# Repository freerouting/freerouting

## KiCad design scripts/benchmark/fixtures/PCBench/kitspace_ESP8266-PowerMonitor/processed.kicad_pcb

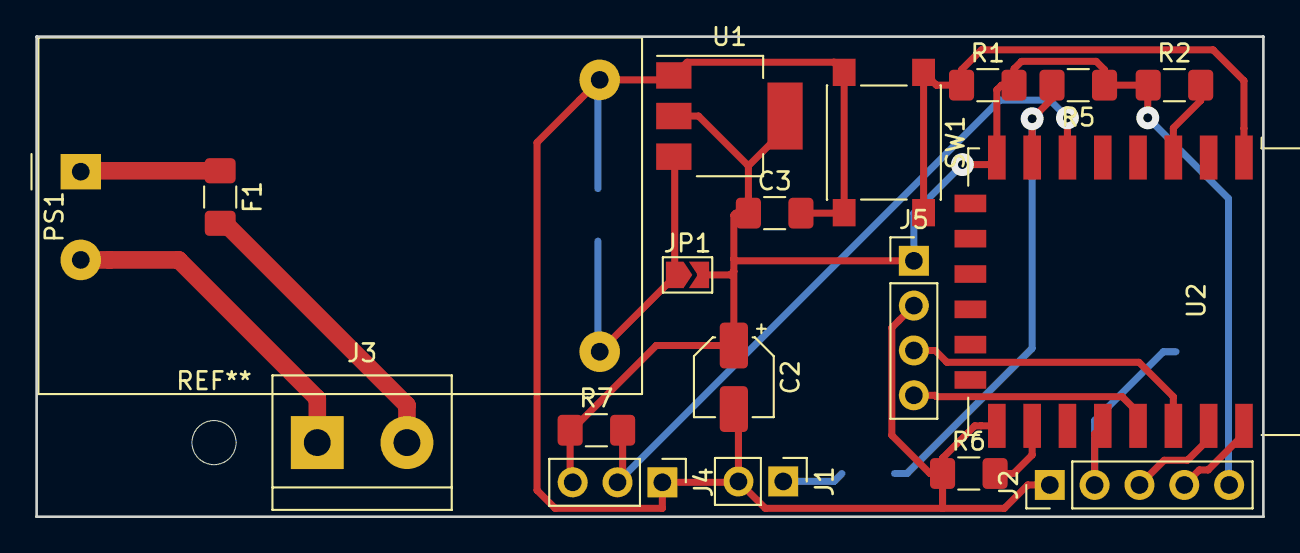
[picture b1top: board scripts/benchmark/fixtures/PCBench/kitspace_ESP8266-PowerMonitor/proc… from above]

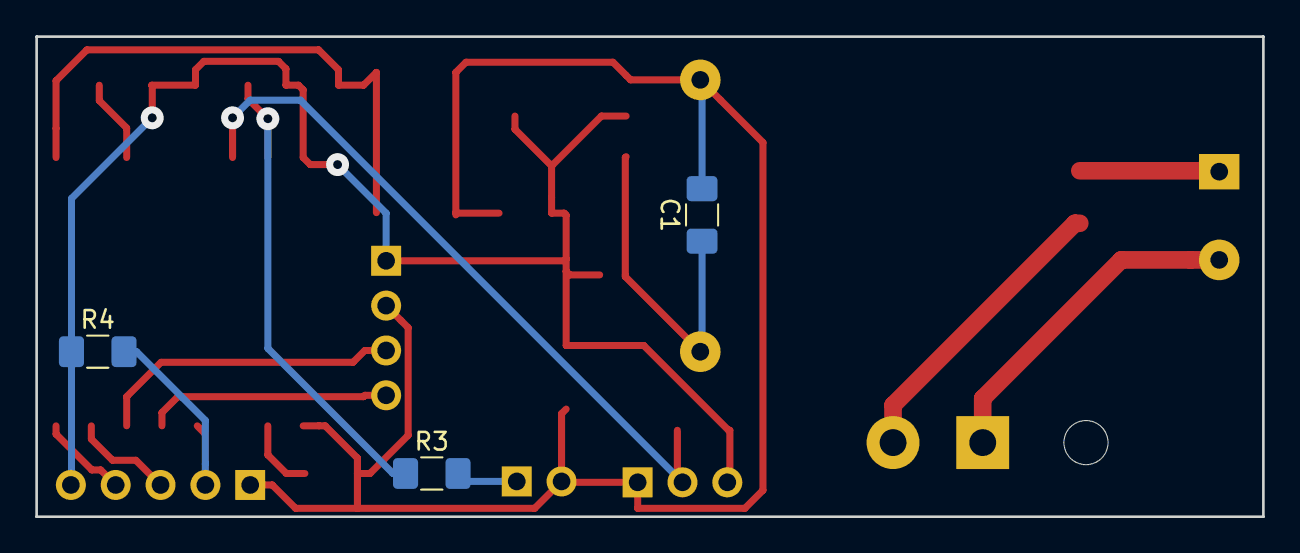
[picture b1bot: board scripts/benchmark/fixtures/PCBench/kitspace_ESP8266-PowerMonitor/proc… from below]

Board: 2 copper layers, 69.5 x 27.2 mm, 21 parts (3 on the bottom side), 17 nets.

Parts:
C1: 0.1uF; C_1206_3216Metric_Pad1.42x1.75mm_HandSolder
C2: 10uF; CP_Elec_4x5.3
C3: 100nF; C_1206_3216Metric_Pad1.42x1.75mm_HandSolder
F1: 100mA; Fuse_1206_3216Metric_Pad1.42x1.75mm_HandSolder
J1: CONN_PULSE; PinHeader_1x02_P2.54mm_Vertical
J2: CONN_PROG; PinHeader_1x05_P2.54mm_Vertical
J3: CONN_AC; TerminalBlock_bornier-2_P5.08mm
J4: CONN_TEMP; PinHeader_1x03_P2.54mm_Vertical
J5: CONN_I2C; PinHeader_1x04_P2.54mm_Vertical
JP1: 3.3V BYPASS; SolderJumper-2_P1.3mm_Open_TrianglePad1.0x1.5mm
PS1: HLK-PM03; Converter_ACDC_HiLink_HLK-PMxx
R1, R2, R4, R5, R6: 10k; R_1206_3216Metric_Pad1.42x1.75mm_HandSolder
R3: 470; R_1206_3216Metric_Pad1.42x1.75mm_HandSolder
R7: 4.7k; R_1206_3216Metric_Pad1.42x1.75mm_HandSolder
SW1: SW_RESET; SW_Push_1P1T_NO_6x6mm_H9.5mm
U1: AMS1117-3.3; SOT-223-3_TabPin2
U2: ESP-12F; ESP-12E

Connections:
+3.3V: C2.1, C3.1, J2.5, J4.3, J5.1, JP1.2, R1.2, R2.1, R4.1, R5.1, R7.1, U1.2, U2.8
AC-L: F1.2, J3.2
AC-N: J3.1, PS1.2
DS18B20_DQ: J4.2, R7.2, U2.6
GND: C1.2, C2.2, C3.2, J1.2, J2.1, J4.1, J5.2, PS1.3, R6.1, SW1.2, U1.1, U2.15
unnamed: C1.1, JP1.1, PS1.4, U1.3
unnamed: F1.1, PS1.1
unnamed: R1.1, SW1.1, U2.1
unnamed: R2.2, U2.3
unnamed: R3.1, R5.2, U2.7
unnamed: R6.2, U2.16
PULSE: J1.1, R3.2
RXD: J2.3, U2.21
SCL: J5.3, U2.20
SDA: J5.4, U2.19
TXD: J2.4, U2.22
_PROG: J2.2, R4.2, U2.18

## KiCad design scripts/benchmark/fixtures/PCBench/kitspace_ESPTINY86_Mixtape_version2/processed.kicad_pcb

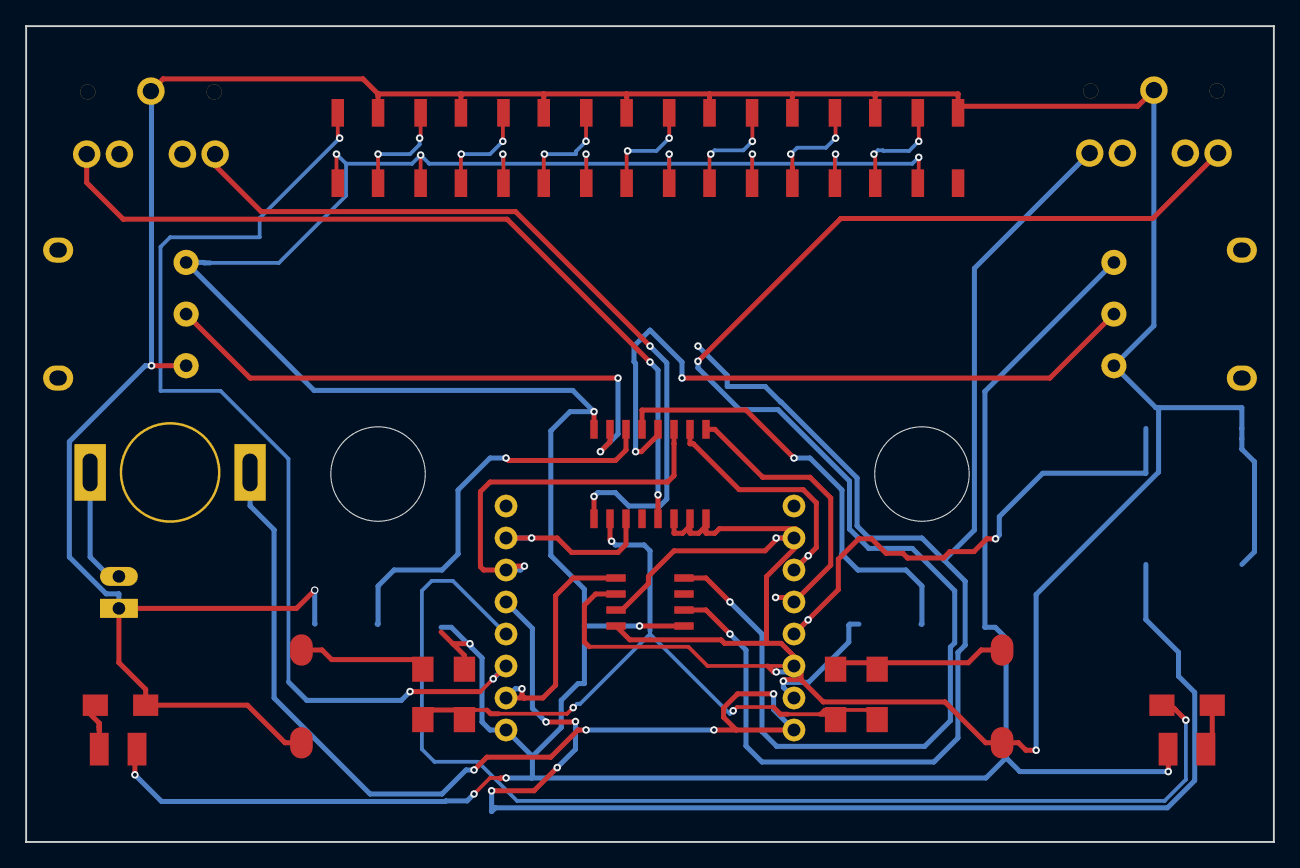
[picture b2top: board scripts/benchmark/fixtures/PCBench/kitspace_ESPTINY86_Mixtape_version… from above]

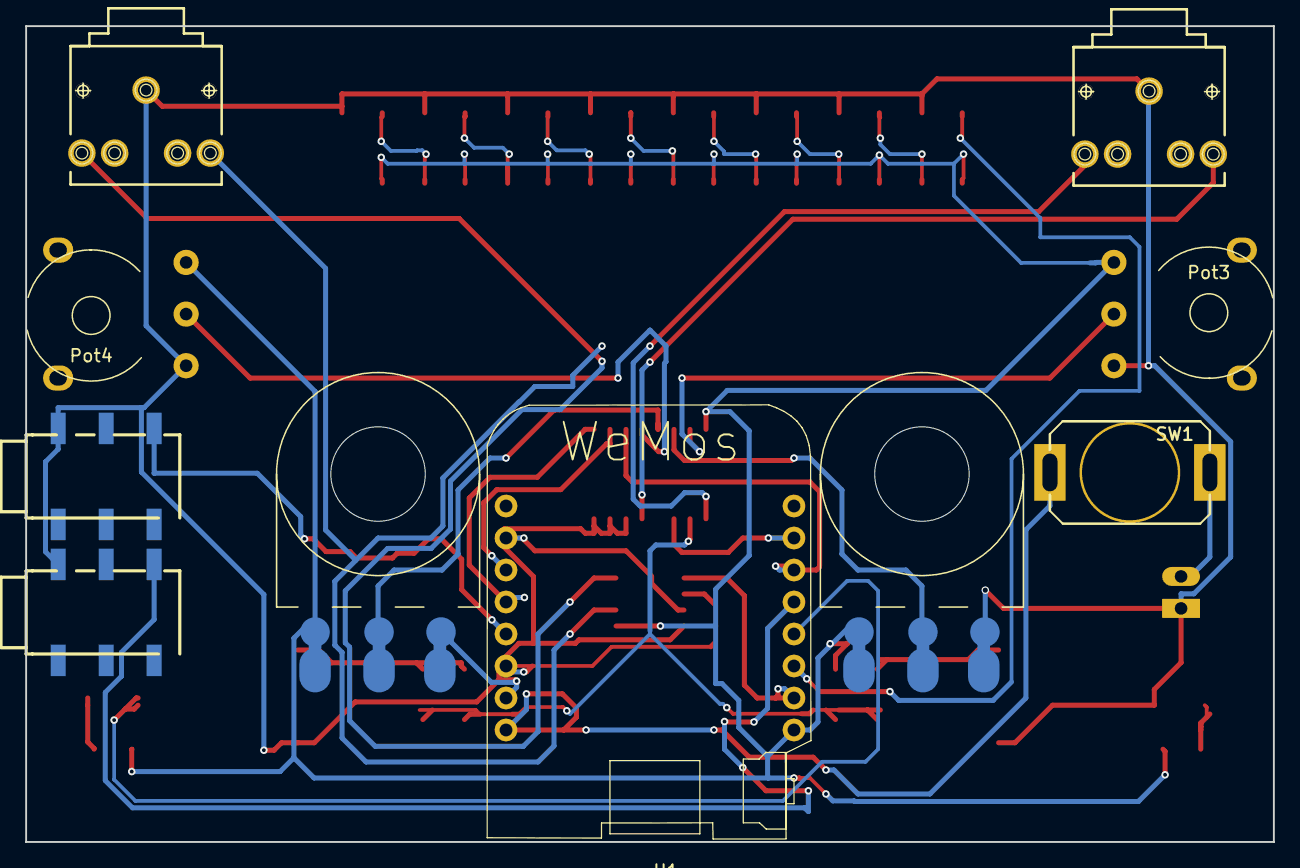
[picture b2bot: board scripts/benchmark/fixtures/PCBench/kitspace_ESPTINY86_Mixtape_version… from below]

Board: 2 copper layers, 99.1 x 64.8 mm, 32 parts (8 on the bottom side), 35 nets.

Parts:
Coconut: LOGO; Coconut_Logo_small_Mask
D1, D2: LED; TopLED_2835
IC1: 4051; 4xxx_SOIC-16W_Pitch1.27mm
IC2: DAC7513_DCN; SOIC-8_3.9x4.9mm_Pitch1.27mm
J1: Bat_EXT; Bat_connector+-
Jack1, Jack3: JACK_TRS_6PINS; AUDIO-Jack_3.5mm_5Pin
Jack2, Jack4: JACK_TRS_6PINS; AUDIO-JACK-3.5mm_SMD_noHole
NEO1, NEO2, NEO3, NEO4, NEO5, NEO6, NEO7, NEO8: LED_SK6813; Mixtape_NEO_WS2812B
Pot1: 10k_big; Potentiometer_backPads_noHole
Pot2: 10k; Potentiometer_backPads_noHole
Pot3: 10k; Potentiometer_wheel_inv
Pot4: 10k; Potentiometer_wheel
R1, R2: R; R_1206_Mixtape
R3, R3_2: 22k; R_1206_Mixtape
R4, R5: 10k; R_1206_Mixtape
SW1: SW_SPST; Push_SWITCH_hole
SW2, SW3: SW_Push; SW_PUSH-8mm_SMD
U1: WeMos_mini; WeMOS_ESP

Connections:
+3V3: D1.2, D2.2, IC1.16, IC2.5, NEO1.1, NEO2.1, NEO3.1, NEO4.1, NEO5.1, NEO6.1, NEO7.1, NEO8.1, Pot1.1, Pot2.1, Pot3.1, Pot4.1, R4.1, U1.16
+5V: SW1.2, U1.1
+BATT: J1.1, SW1.1
Buttons: IC1.2, R3.2, R3_2.2, R4.2, R5.2
CV1: IC1.1, Jack3.2
CV2: IC1.5, Jack3.3
D3: Jack2.2, U1.4
D5: Jack4.2, U1.12
GND: IC1.6, IC1.7, IC1.8, IC2.4, J1.2, Jack1.1, Jack2.1, Jack3.1, Jack4.1, NEO1.3, NEO2.3, NEO3.3, NEO4.3, NEO5.3, NEO6.3, NEO7.3, NEO8.3, Pot1.3, Pot2.3, Pot3.3, Pot4.3, R2.1, SW2.2, SW3.2, U1.2
L-Out: IC2.6, Jack1.3
Led1_pulldown: R1.2, U1.13
NEO-Pixel: NEO8.4, U1.14
unnamed: D1.1, R1.1
unnamed: D2.1, R2.2
unnamed: IC1.3, U1.10
unnamed: IC1.9, U1.5
unnamed: IC1.10, U1.6
unnamed: IC1.11, U1.11
unnamed: IC2.1, U1.15
unnamed: IC2.3, U1.7
unnamed: NEO1.4, NEO2.2
unnamed: NEO2.4, NEO3.2
unnamed: NEO3.4, NEO4.2
unnamed: NEO4.4, NEO5.2
unnamed: NEO5.4, NEO6.2
unnamed: NEO6.4, NEO7.2
unnamed: NEO7.4, NEO8.2
unnamed: R3.1, R3_2.1, SW3.1
unnamed: R5.1, SW2.1
Pot1: IC1.13, Pot1.2
Pot2: IC1.14, Pot2.2
Pot3: IC1.15, Pot3.2
Pot4: IC1.12, Pot4.2
R-Out: IC2.8, Jack1.2
problem: IC2.2, U1.3

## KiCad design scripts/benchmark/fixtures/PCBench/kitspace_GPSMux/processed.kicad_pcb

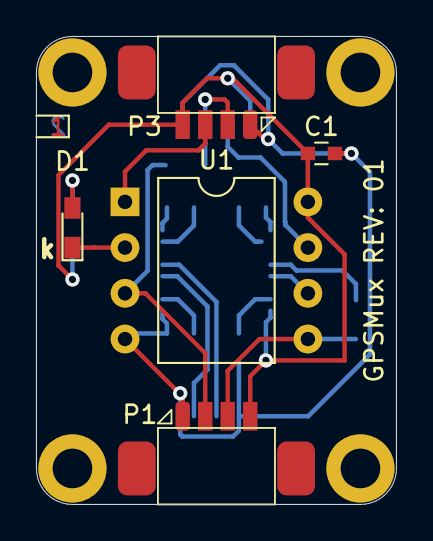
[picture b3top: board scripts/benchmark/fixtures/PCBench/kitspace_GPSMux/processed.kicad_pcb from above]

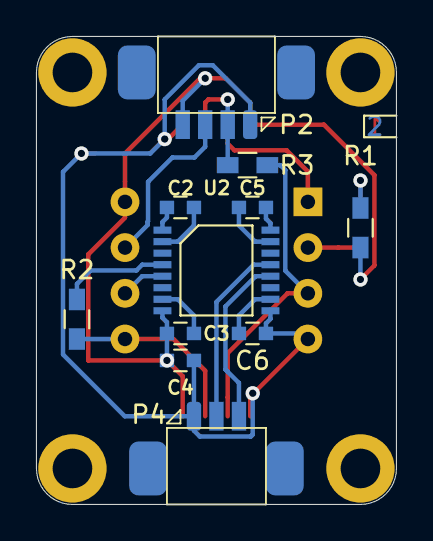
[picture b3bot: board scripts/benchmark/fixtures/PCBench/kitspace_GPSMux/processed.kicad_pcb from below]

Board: 2 copper layers, 20.0 x 26.0 mm, 16 parts (11 on the bottom side), 19 nets.

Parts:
C1, C2, C3, C4, C5, C6: 100nF; C_0603
D1: LY Q396; LED_0603_HandSoldering
P1: ICSP; 53261-0471
P2: GPS1; 53261-0471
P3: GPS2; 53261-0471
P4: LLU; 53261-0371
R1: 120R; R_0603_HandSoldering
R2, R3: 0R; R_0603_HandSoldering
U1: CY8C27143-24PXI; DIP-8_W10.16mm
U2: ADM3101EARQZ; QSOP16

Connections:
+3.3V: C1.1, C3.2, C4.1, P1.4, P2.4, P3.4, R1.2, U1.8, U2.8
GND: C1.2, C4.2, C6.1, P1.1, P2.1, P3.1, P4.1, U1.4, U2.9
I2C_SCL: P1.2, R3.2, U1.3
I2C_SDA: P1.3, R2.1, U1.5
unnamed: C2.1, U2.1
unnamed: C2.2, U2.2
unnamed: C3.1, U2.7
unnamed: C5.1, U2.16
unnamed: C5.2, U2.15
unnamed: C6.2, U2.10
unnamed: D1.1, U1.2
unnamed: D1.2, R1.1
RX: R2.2, U2.4
RX1: P2.3, U1.7
RX2: P3.3, U1.1
RX_232: P4.2, U2.13
TX: U1.6, U2.5
TX_232: P4.3, U2.12
TX_GPS: P2.2, P3.2, R3.1
